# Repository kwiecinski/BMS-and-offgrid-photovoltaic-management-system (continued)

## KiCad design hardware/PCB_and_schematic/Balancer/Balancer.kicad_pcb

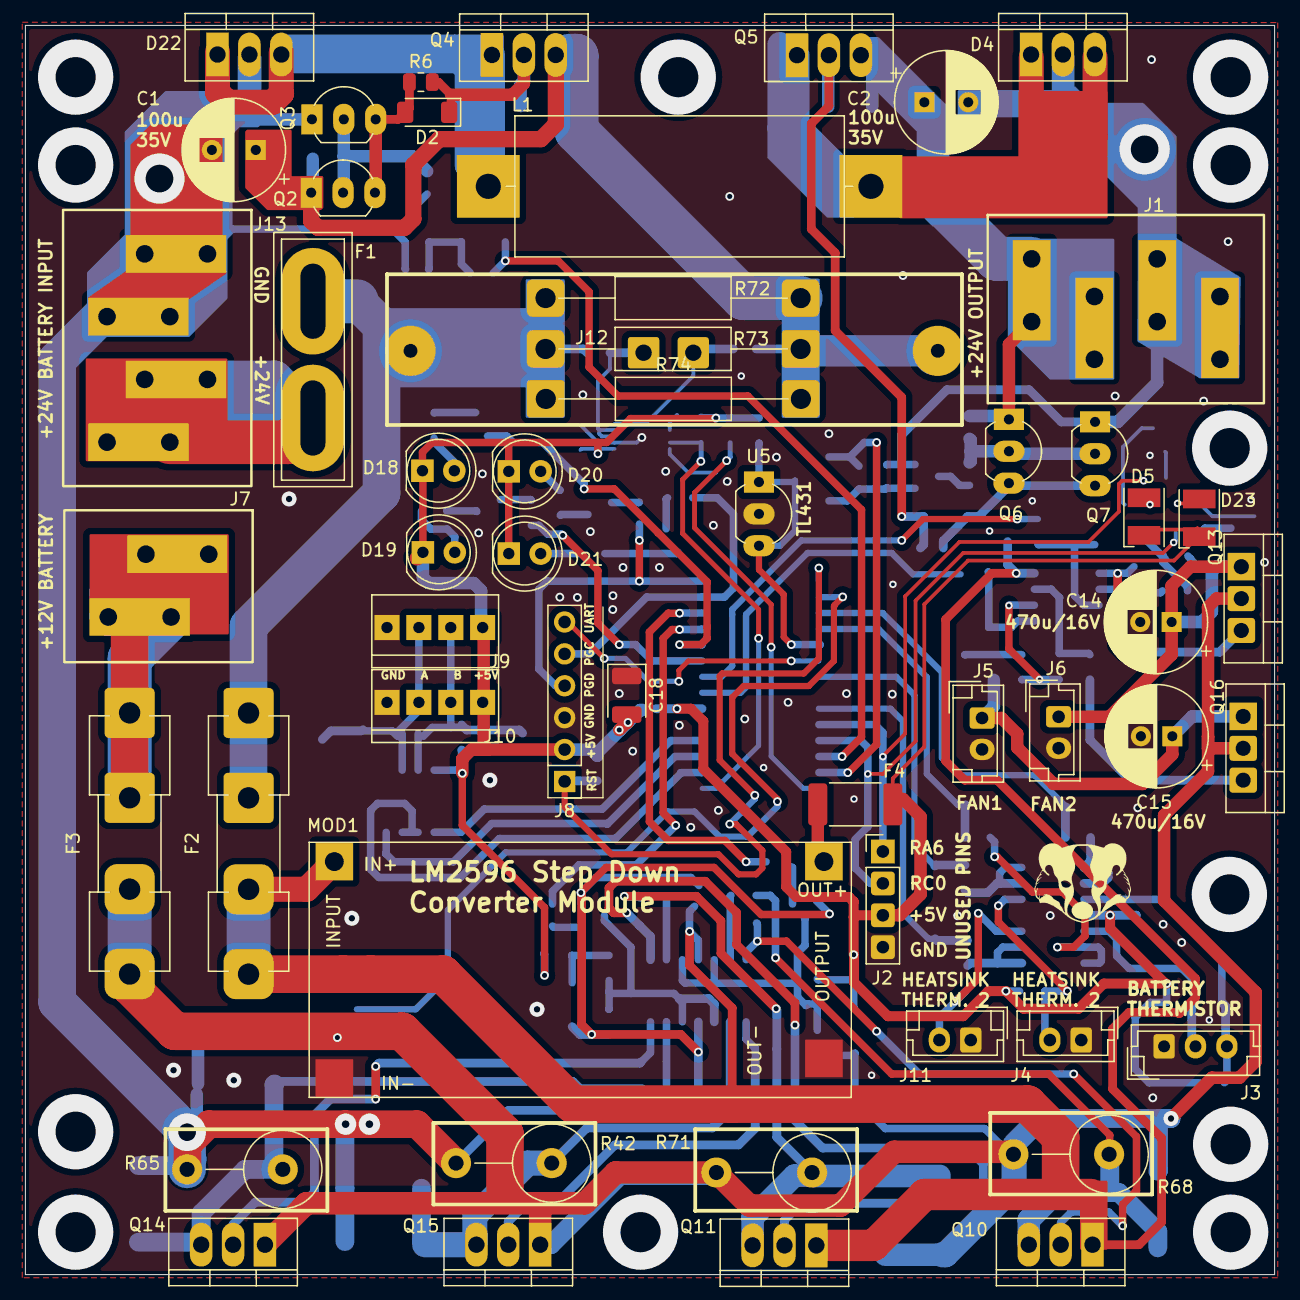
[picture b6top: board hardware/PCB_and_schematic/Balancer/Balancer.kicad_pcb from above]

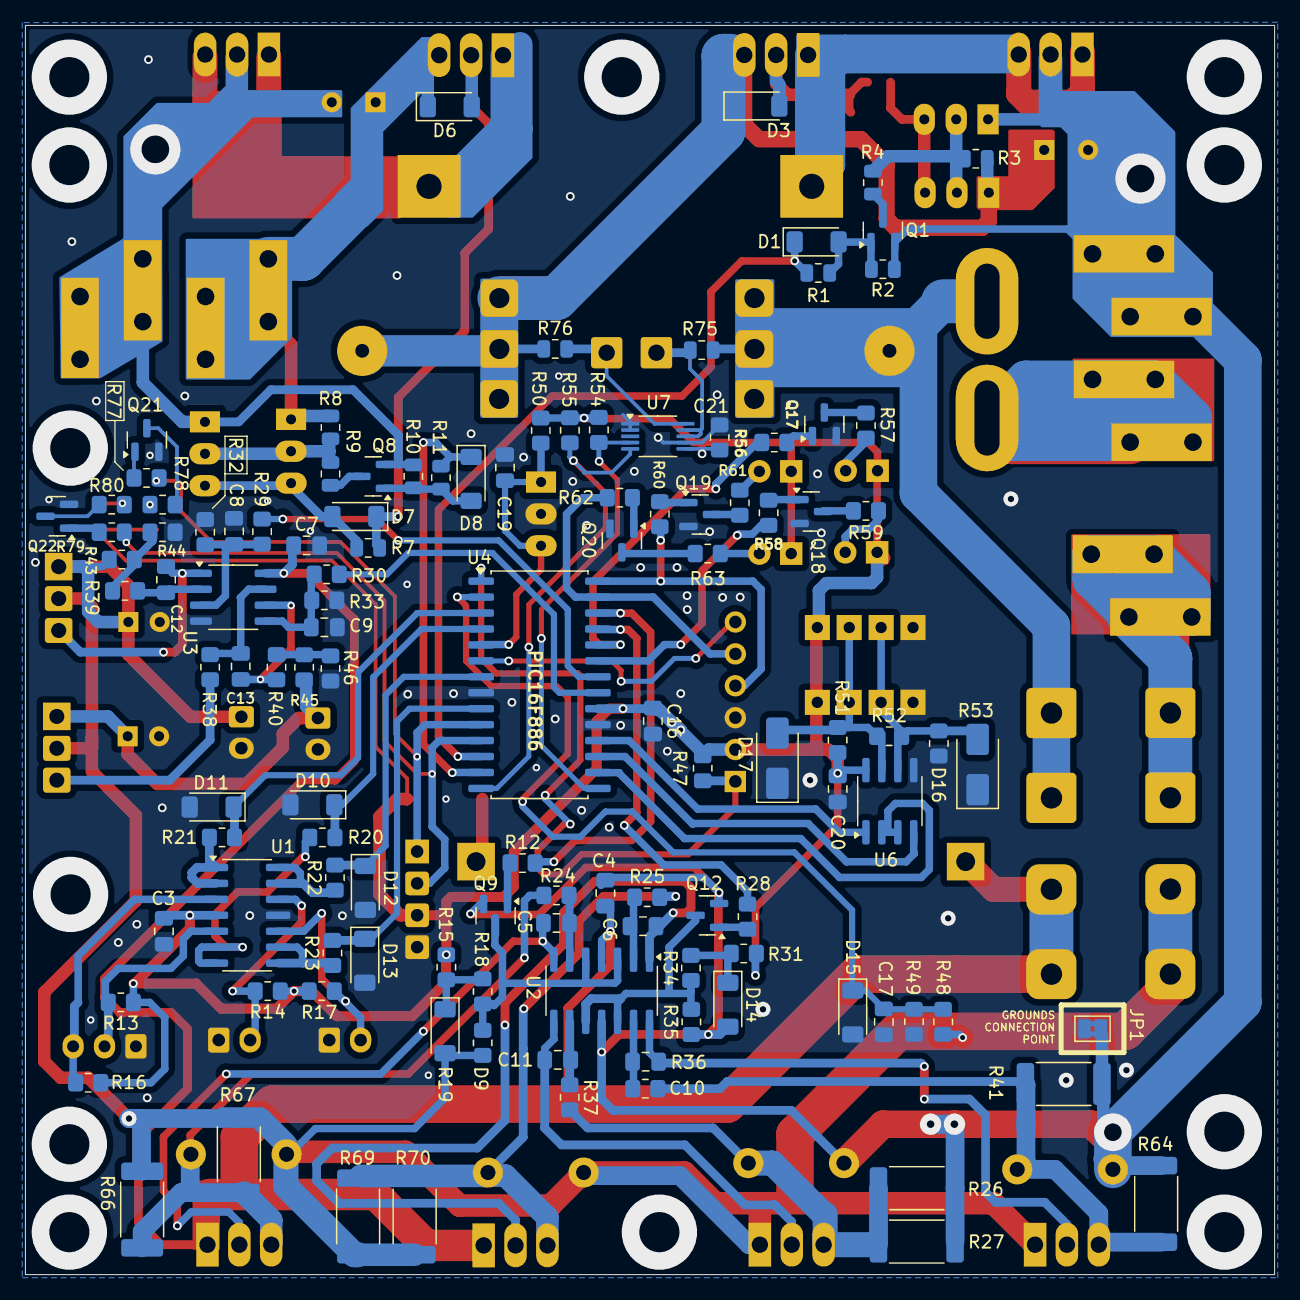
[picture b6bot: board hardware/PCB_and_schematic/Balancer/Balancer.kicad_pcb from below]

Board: 2 copper layers, 99.5 x 99.5 mm, 173 parts (118 on the bottom side), 107 nets.

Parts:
C1, C2: 100u/35V; CP_Radial_D8.0mm_P3.50mm
C3, C4, C5, C6, C7, C10, C11, C12, C13, C16, C17, C19, C20: 100n; C_0805_2012Metric_Pad1.18x1.45mm_HandSolder
C8, C9: 1u; C_0805_2012Metric_Pad1.18x1.45mm_HandSolder
C14, C15: 470u/16V; CP_Radial_D8.0mm_P2.50mm
C18: 100u/6,3V (JA8); CP_EIA-3528-21_Kemet-B
C21: 100n; R_0805_2012Metric_Pad1.20x1.40mm_HandSolder
D1, D2, D7, D8: LL4148; D_MiniMELF
D3, D6: 18V; D_MiniMELF
D4, D22: D_Schottky_Dual_CommonAnode_KAK_Parallel; TO-220-3_V_Thick_Pads
D5, D23: LED; LED_PLCC-2_3.4x3.0mm_KA
D9, D10, D11, D12, D13, D14, D15: 3V3; D_MiniMELF
D16, D17: D_TVS; D_SMA
D18, D19, D20, D21: LED; LED_D5.0mm
F1: 6,3A; Fuse_Blade_ATO_directSolder
F2: 2A; Fuseholder_Clip-5x20mm_Eaton_1A5601-01_Inline_P20.80x6.76mm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
F3: 6,3A; Fuseholder_Clip-5x20mm_Eaton_1A5601-01_Inline_P20.80x6.76mm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
F4: 2A; Fuse_2512_6332Metric_Pad1.52x3.35mm_HandSolder
J1: BATT_OUT; Flat-6,3mm-connector-4P
J2: Conn_01x04; PinHeader_1x04_P2.54mm_Vertical
J3: Conn_01x03; JST_EH_B3B-EH-A_1x03_P2.50mm_Vertical
J4, J11: HEATSING_TEMP1; JST_EH_B2B-EH-A_1x02_P2.50mm_Vertical
J5: FAN1; JST_EH_B2B-EH-A_1x02_P2.50mm_Vertical
J6: FAN2; JST_EH_B2B-EH-A_1x02_P2.50mm_Vertical
J7: BATT_12V; Flat-6,3mm-connector-2P
J8: ICP; PinHeader_1x06_P2.54mm_Vertical
J9, J10: RS485; Conn-01x04-N25-W4P
J12: External Current Shunt; Hirose_DF63M-2P-3.96DSA_1x02_P3.96mm_Vertical
J13: BATT_IN; Flat-6,3mm-connector-4P
JP1: GND_Bridged; SolderJumper-2_P1.3mm_Bridged2Bar_Pad1.0x1.5mm
L1: L; L_Axial_L26.0mm_D11.0mm_P30.48mm_Horizontal_Fastron_77A
MOD1: LM2596-Step-Down; LM2596-Step-Down-Conv
Q1, Q8, Q9, Q12, Q17, Q18, Q19, Q20, Q21, Q22: BC817; SOT-23
Q2, Q6: BC337; TO-92_Inline_Wide
Q3, Q7: BC327; TO-92_Inline_Wide
Q4, Q5: PMOS; TO-220-3_V_Thick_Pads
Q10, Q11, Q14, Q15: NPN; TO-220-3_V_Thick_Pads
Q13, Q16: BD238; TO-220-3_Vertical-little-bigger pads
R1, R11: 4k7; R_0805_2012Metric
R2, R3, R8, R10: 10k; R_0805_2012Metric
R4, R6, R9: 1k; R_0805_2012Metric
R5: 20A/75mV; Resistor-Power-5W-L22-W10
R7: 100R; R_0805_2012Metric
R12, R28, R45, R47, R54, R55: 10k; R_0805_2012Metric_Pad1.20x1.40mm_HandSolder
R13, R14, R16, R17: 150k; R_0805_2012Metric_Pad1.20x1.40mm_HandSolder
R15, R18, R19, R31, R34, R35, R52: 120R; R_0805_2012Metric_Pad1.20x1.40mm_HandSolder
R20, R21, R22, R23, R38, R50: 1k; R_0805_2012Metric_Pad1.20x1.40mm_HandSolder
R24, R25, R36, R37, R39, R40: 0R; R_0805_2012Metric_Pad1.20x1.40mm_HandSolder
R26, R27, R41, R64, R66, R67, R69, R70: 0R1; R_2512_6332Metric_Pad1.40x3.35mm_HandSolder
R29, R30: 2k2; R_0805_2012Metric_Pad1.20x1.40mm_HandSolder
R32, R33: 100k; R_0805_2012Metric_Pad1.20x1.40mm_HandSolder
R42, R65, R68, R71: 0R1; R_Axial_DIN0617_L17.0mm_D6.0mm_P7.62mm_Vertical
R43, R56, R58, R60, R62, R77, R79: 10K; R_0805_2012Metric_Pad1.20x1.40mm_HandSolder
R44, R46: 6k2; R_0805_2012Metric_Pad1.20x1.40mm_HandSolder
R48: 6k8; R_0805_2012Metric_Pad1.20x1.40mm_HandSolder
R49: 1k3; R_0805_2012Metric_Pad1.20x1.40mm_HandSolder
R51, R53: 510R; R_0805_2012Metric_Pad1.20x1.40mm_HandSolder
R57, R59, R61, R63, R78, R80: 220R; R_0805_2012Metric_Pad1.20x1.40mm_HandSolder
R72, R73, R74: 20A/75mV; R_Axial_DIN0309_L9.0mm_D3.2mm_P20.32mm_Horizontal
R75, R76: 0R; R_0805_2012Metric
U1, U2: LM324; SOIC-14_3.9x8.7mm_P1.27mm
U3: LM358; SO-8_3.9x4.9mm_P1.27mm
U4: PIC16F886-IP; SOIC-28W_7.5x17.9mm_P1.27mm
U5: TL431LP; TO-92_Inline_Wide
U6: ST485; SOIC-8_3.9x4.9mm_P1.27mm
U7: INA226; VSSOP-10_3x3mm_P0.5mm

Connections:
+5V: C3.1, C16.1, C18.2, C20.1, C21.1, D5.1 (K), D18.1 (K), D19.1 (K), D20.1 (K), D21.1 (K), D23.1 (K), F4.2, J2.3, J8.2, J9.1, J10.1, R13.1, R14.1, R15.2, R16.1, R17.1, R31.2, R47.1, R50.1, R51.1, R54.1, R55.1, U1.4 (V+), U4.20 (VDD), U6.8 (VCC), U7.6 (VS)
+BATT_12V: D9.2 (A), F3.1, Q13.2 (C), Q14.1 (C), Q15.1 (C), Q16.2 (C), R19.1, R48.1, R66.2, R67.2, R68.2, R69.2, R70.2, R71.2
+BATT_24V: C4.1, C7.1, F2.1, MOD1.2 (IN+), Q10.1 (C), Q11.1 (C), U2.4 (V+), U3.8 (V+)
/BMS_microcontroller/RS485_A: D16.2 (A2), J9.3, J10.3, R52.2, R53.1, U6.6 (A)
/BMS_microcontroller/RS485_B: D17.2 (A2), J9.2, J10.2, R51.2, R52.1, U6.7 (B)
BALANCE_ON_12V: R28.2, U4.25 (P1D/AN11/RB4)
BALANCE_ON_24V: R12.2, U4.26 (~T1G/AN13/RB5)
CLOCK: R55.2, U4.14 (RC3/SCK/SCL), U7.5 (SCL)
DBG_UART: J8.6, U4.6 (T0CKI/C1OUT/RA4)
DC_LINE_24V: C2.1, D6.1 (K), J1.1, J1.2, Q5.3 (S), Q6.1 (C), R8.2
GND: C3.2, C7.2, C8.2, C9.2, C14.2, C15.2, C16.2, C17.2, C18.1, C19.2, C20.2, C21.2, D10.2 (A), D11.2 (A), D12.2 (A), D13.2 (A), D15.2 (A), D16.1 (A1), D17.1 (A1), J2.4, J3.1, J4.1, J5.2, J6.2, J8.3, J9.4, J10.4, J11.1, JP1.1 (A), MOD1.1 (IN-), MOD1.3 (OUT-), Q17.2 (E), Q18.2 (E), Q19.2 (E), Q20.2 (E), Q21.2 (E), Q22.2 (E), R32.1, R33.1, R44.1, R46.1, R49.2, R53.2, U1.11 (V-), U3.4 (V-), U4.8 (VSS), U4.19 (VSS), U5.2 (A), U6.5 (GND), U7.1 (A1), U7.2 (A0), U7.7 (GND)
GNDA: C1.2, C2.2, C4.2, D4.2 (A), D14.2 (A), D22.2 (A), J1.3, J1.4, J13.1, J13.2, JP1.2 (B), Q1.2 (E), Q3.1 (C), Q7.1 (C), Q8.2 (E), Q9.2 (E), Q12.2 (E), R2.1, R10.1, R26.2, R27.2, R35.1, R41.2, R42.2, R64.2, R65.2, U2.11 (V-)
LED1: R56.2, U4.24 (PGM/C12IN2-/AN8/RB3)
LED2: R58.2, U4.23 (P1B/AN8/RB2)
unnamed: C13.1, R38.2, U3.7
unnamed: D1.2 (A), Q1.1 (B), R1.2, R2.2
unnamed: D2.2 (A), Q2.3 (E), Q3.3 (E), R6.1
unnamed: D2.1 (K), D3.2 (A), Q4.2 (G), R6.2
unnamed: C1.1, D3.1 (K), Q2.1 (C), Q4.3 (S), R3.2, R5.2, R72.2, R73.2, R74.2, R76.1
unnamed: D5.2 (A), R78.2
unnamed: D6.2 (A), D7.1 (K), Q5.2 (G), R7.2
unnamed: D7.2 (A), Q6.3 (E), Q7.3 (E), R7.1
unnamed: D8.2 (A), Q8.1 (B), R10.2, R11.2
unnamed: D9.1 (K), R15.1, R18.2
unnamed: D14.1 (K), R31.1, R34.2
unnamed: D18.2 (A), R57.2
unnamed: D19.2 (A), R59.2
unnamed: D20.2 (A), R61.2
unnamed: D21.2 (A), R63.2
unnamed: D23.2 (A), R80.2
unnamed: F1.2, F2.2, R5.1, R72.1, R73.1, R74.1, R75.1
unnamed: J3.2, R13.2, U1.5 (+)
unnamed: J3.3, R16.2, U1.3 (+)
unnamed: J4.2, R14.2, U1.12 (+)
unnamed: C15.1, J5.1, Q16.1 (E), R45.2
unnamed: C14.1, J6.1, Q13.1 (E), R43.2
unnamed: F3.2, J7.1, J7.2
unnamed: J11.2, R17.2, U1.10 (+)
unnamed: F1.1, J13.3, J13.4
unnamed: F4.1, MOD1.4 (OUT+)
unnamed: Q1.3 (C), R4.1
unnamed: Q2.2 (B), Q3.2 (B), R3.1, R4.2
unnamed: D22.1 (K), D22.3 (K), L1.1, Q4.1 (D)
unnamed: D4.1 (K), D4.3 (K), L1.2, Q5.1 (D)
unnamed: Q6.2 (B), Q7.2 (B), R8.1, R9.2
unnamed: Q8.3 (C), R9.1
unnamed: Q9.1 (B), R12.1
unnamed: Q9.3 (C), R18.1, R19.2, U2.3 (+), U2.5 (+)
unnamed: C5.1, Q10.2 (B), U2.7
unnamed: Q10.3 (E), R24.2, R66.1, R67.1, R68.1
unnamed: C6.1, Q11.2 (B), U2.1
unnamed: Q11.3 (E), R25.2, R69.1, R70.1, R71.1
unnamed: Q12.1 (B), R28.1
unnamed: Q12.3 (C), R34.1, R35.2, U2.10 (+), U2.12 (+)
unnamed: C12.1, Q13.3 (B), U3.1
unnamed: C10.1, Q14.2 (B), U2.14
unnamed: Q14.3 (E), R36.2, R41.1, R64.1, R65.1
unnamed: C11.1, Q15.2 (B), U2.8
unnamed: Q15.3 (E), R26.1, R27.1, R37.2, R42.1
unnamed: Q16.3 (B), R38.1
unnamed: Q17.1 (B), R56.1
unnamed: Q17.3 (C), R57.1
unnamed: Q18.1 (B), R58.1
unnamed: Q18.3 (C), R59.1
unnamed: Q19.1 (B), R60.1
unnamed: Q19.3 (C), R61.1
unnamed: Q20.1 (B), R62.1
unnamed: Q20.3 (C), R63.1
unnamed: Q21.1 (B), R77.1
unnamed: Q21.3 (C), R78.1
unnamed: Q22.1 (B), R79.1
unnamed: Q22.3 (C), R80.1
unnamed: R39.2, R43.1, R44.2
unnamed: R40.2, R45.1, R46.2
unnamed: R21.1, U1.1, U1.2 (-)
unnamed: R20.1, U1.6 (-), U1.7
unnamed: R23.1, U1.8, U1.9 (-)
unnamed: R22.1, U1.13 (-), U1.14
unnamed: C6.2, R25.1, U2.2 (-)
unnamed: C5.2, R24.1, U2.6 (-)
unnamed: C11.2, R37.1, U2.9 (-)
unnamed: C10.2, R36.1, U2.13 (-)
unnamed: C8.1, R29.2, R32.2, U3.3 (+)
unnamed: C12.2, R39.1, U3.2 (-)
unnamed: C9.1, R30.2, R33.2, U3.5 (+)
unnamed: C13.2, R40.1, U3.6 (-)
PGC: J8.5, R62.2, U4.27 (ICSPCLK/RB6)
PGD: J8.4, R60.2, U4.28 (ICSPDAT/RB7)
PWM_OUT1: R30.1, U4.21 (INT/AN12/RB0)
PWM_OUT2: R29.1, U4.22 (P1C/AN10/RB1)
PWM_OUT_CHRG: D8.1 (K), R11.1, U4.13 (RC2/P1A/CCP1)
PWM_OUT_DISCH: D1.1 (K), R1.1, U4.12 (RC1/T1OSI/CCP2)
RA6: J2.1, R77.2, U4.10 (CLKOUT/OSC2/RA6)
RC0: J2.2, R79.2, U4.11 (RC0/T1OSO/T1CK1)
RS232_RX: U4.18 (RC7/RX/DT), U6.1 (RO)
RS232_TX: U4.17 (RC6/TX/CK), U6.4 (DI)
RS485_OUTPUT_ENABLE: U4.16 (RC5/SDO), U6.2 (~RE), U6.3 (DE)
RST: J8.1, R47.2, U4.1 (RE3/~MCLR/Vpp)
R_shunt_H: J12.2, R75.2, U7.8 (Vbus), U7.9 (Vin-)
R_shunt_L: J12.1, R76.2, U7.10 (Vin+)
SDA: R54.2, U4.15 (RC4/SDI/SDA), U7.4 (SDA)
TEMP_AKU_12V: D11.1 (K), R21.2, U4.3 (C12IN1-/AN1/RA1)
TEMP_AKU_24V: D10.1 (K), R20.2, U4.4 (CVref/C2IN1+/Vref-/AN2/RA2)
TEMP_HEAT_SINK_12V: D13.1 (K), R23.2, U4.9 (CLKIN/OSC1/RA7)
TEMP_HEAT_SINK_24V: D12.1 (K), R22.2, U4.7 (~SS/C2OUT/AN4/RA5)
VOLTAGE_BATT_12V: C17.1, D15.1 (K), R48.2, R49.1, U4.2 (ULPWU/C12IN0-/AN0/RA0)
VREF_2V5: C19.1, R50.2, U4.5 (C1IN+/Vref+/AN3/RA3), U5.1 (REF), U5.3 (K)

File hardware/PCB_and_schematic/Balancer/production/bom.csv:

Designator,Footprint,Quantity,Value,LCSC Part #
"C1, C2",CP_Radial_D8.0mm_P3.50mm,2,100u/35V,
"C10, C11, C12, C13, C16, C17, C19, C20, C21, C3, C4, C5, C6, C7",0805,14,100n,
"C14, C15",CP_Radial_D8.0mm_P2.50mm,2,470u/16V,
C18,CP_EIA-3528-21_Kemet-B,1,"100u/6,3V",
"C8, C9",0805,2,1u,
"D1, D2, D7, D8",D_MiniMELF,4,LL4148,
"D10, D11, D12, D13, D14, D15, D9",D_MiniMELF,7,3V3,
"D16, D17",D_SMA,2,D_TVS,
"D18, D19, D20, D21",LED_D5.0mm,4,LED,
"D22, D4",TO-220-3_V_Thick_Pads,2,D_Schottky_Dual_CommonAnode_KAK_Parallel,
"D23, D5",LED_PLCC-2_3.4x3.0mm_KA,2,LED,
"D3, D6",D_MiniMELF,2,18V,
F1,Fuse_Blade_ATO_directSolder,1,"6,3A",
F2,Fuseholder_Clip-5x20mm_Eaton_1A5601-01_Inline_P20.80x6.76mm_D1.70mm_Horizontal,1,2A,
F3,Fuseholder_Clip-5x20mm_Eaton_1A5601-01_Inline_P20.80x6.76mm_D1.70mm_Horizontal,1,"6,3A",
F4,2512,1,2A,
J1,"Flat-6,3mm-connector-4P",1,BATT_OUT,
J10,PinHeader_1x04_P2.54mm_Vertical,1,RS485,
"J11, J4",JST_EH_B2B-EH-A_1x02_P2.50mm_Vertical,2,HEATSING_TEMP1,
J12,Hirose_DF63M-2P-3.96DSA_1x02_P3.96mm_Vertical,1,External Current Shunt,
J13,"Flat-6,3mm-connector-4P",1,BATT_IN,
J2,PinHeader_1x04_P2.54mm_Vertical,1,Conn_01x04,
J3,JST_EH_B3B-EH-A_1x03_P2.50mm_Vertical,1,Conn_01x03,
J5,JST_EH_B2B-EH-A_1x02_P2.50mm_Vertical,1,FAN1,
J6,JST_EH_B2B-EH-A_1x02_P2.50mm_Vertical,1,FAN2,
J7,"Flat-6,3mm-connector-2P",1,BATT_12V,
J8,PinHeader_1x06_P2.54mm_Vertical,1,ICP,
JP1,SolderJumper-2_P1.3mm_Bridged2Bar_Pad1.0x1.5mm,1,GND_Bridged,
L1,L_Axial_L26.0mm_D11.0mm_P30.48mm_Horizontal_Fastron_77A,1,L,
MOD1,LM2596-Step-Down-Conv,1,LM2596-Step-Down,
"Q1, Q12, Q17, Q18, Q19, Q20, Q21, Q22, Q8, Q9",SOT-23,10,BC817,
"Q10, Q11, Q14, Q15",TO-220-3_V_Thick_Pads,4,NPN,
"Q13, Q16",TO-126-3_Vertical,2,BD238,
"Q2, Q6",TO-92_Inline_Wide,2,BC337,
"Q3, Q7",TO-92_Inline_Wide,2,BC327,
"Q4, Q5",TO-220-3_V_Thick_Pads,2,PMOS,
"R1, R11",0805,2,4k7,
"R10, R12, R2, R28, R3, R43, R45, R47, R54, R55, R56, R58, R60, R62, R77, R79, R8",0805,17,10k,
"R13, R14, R16, R17",0805,4,150k,
"R15, R18, R19, R31, R34, R35, R52",0805,7,120R,
"R20, R21, R22, R23, R38, R4, R50, R6, R9",0805,9,1k,
"R24, R25, R36, R37, R39, R40, R75, R76",0805,8,0R,
"R26, R27, R41, R64, R66, R67, R69, R70",2512,8,0R1,
"R29, R30",0805,2,2k2,
"R32, R33",0805,2,100k,
"R42, R65, R68, R71",R_Axial_DIN0617_L17.0mm_D6.0mm_P7.62mm_Vertical,4,0R1,
"R44, R46",0805,2,6k2,
R48,0805,1,6k8,
R49,0805,1,1k3,
R5,Resistor-Power-5W-L22-W10,1,20A/75mV,
"R51, R53",0805,2,510R,
"R57, R59, R61, R63, R78, R80",0805,6,220R,
R7,0805,1,100R,
"R72, R73, R74",R_Axial_DIN0309_L9.0mm_D3.2mm_P20.32mm_Horizontal,3,20A/75mV,
"U1, U2",SOIC-14_3.9x8.7mm_P1.27mm,2,LM324,
U3,SO-8_3.9x4.9mm_P1.27mm,1,LM358,
U4,SOIC-28W_7.5x17.9mm_P1.27mm,1,PIC16F886-IP,
U5,TO-92_Inline_Wide,1,TL431LP,
U6,SOIC-8_3.9x4.9mm_P1.27mm,1,ST485,
U7,VSSOP-10_3x3mm_P0.5mm,1,INA226,
